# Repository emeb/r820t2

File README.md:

# r820t2
Breakout PCB design and STM32F0 firmware for the Rafael R820T2 tuner chip

Contents
--------

doc - documents for the chip and PCB design. This includes both the orginal
mfgs datasheet as well as schematic and BOM for the PCB design.

f030_r820t2 - STM32F030 firmware. A simple serial command line interface
to access registers and set frequency & gain parameters.

r820t2_breakout - KiCAD PCB design.

LICENSE
-------

The PCB design is licensed separately from the driver code. Please see
the LICENSE files within each sub-directory.

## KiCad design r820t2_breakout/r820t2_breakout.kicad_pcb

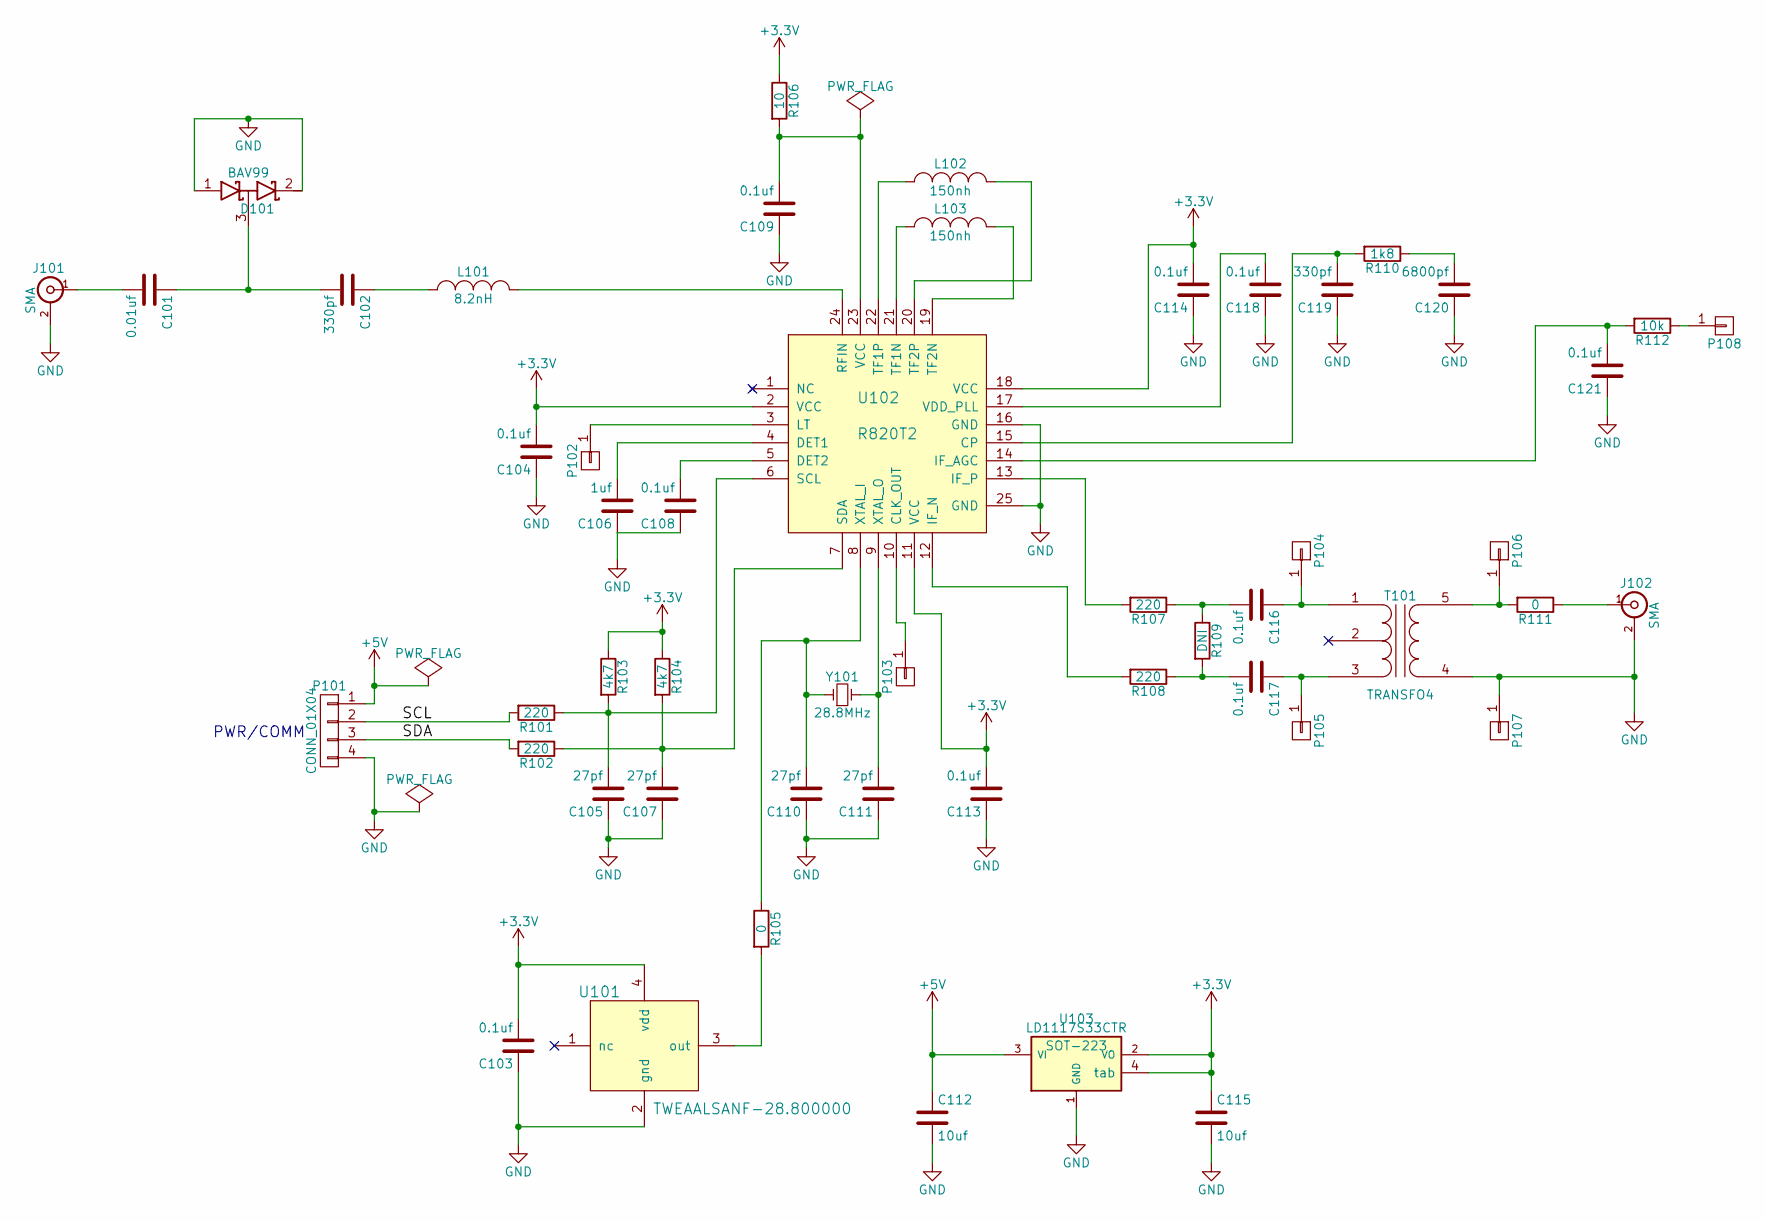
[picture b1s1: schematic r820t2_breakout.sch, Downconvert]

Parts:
C101: 0.01uf; C_0603_HandSoldering
C102, C119: 330pf; C_0603_HandSoldering
C103, C104, C108, C109, C113, C114, C116, C117, C118, C121: 0.1uf; C_0603_HandSoldering
C105, C107, C110, C111: 27pf; C_0603_HandSoldering
C106: 1uf; C_0603_HandSoldering
C112, C115: 10uf; C_0805_HandSoldering
C120: 6800pf; C_0603_HandSoldering
D101: BAV99; SOT-23
J101, J102: SMA; SMA_END
L101: 8.2nH; R_0603_HandSoldering
L102, L103: 150nh; R_0603_HandSoldering
P101: CONN_01X04; Pin_Header_Straight_1x04_Pitch2.54mm
P102, P103, P104, P105, P106, P107, P108: CONN_01X01; PINTST
R101, R102, R107, R108: 220; R_0603_HandSoldering
R103, R104: 4k7; R_0603_HandSoldering
R105, R111: 0; R_0603_HandSoldering
R106: 10; R_0603_HandSoldering
R109: DNI; R_0603_HandSoldering
R110: 1k8; R_0603_HandSoldering
R112: 10k; R_0603_HandSoldering
T101: TRANSFO4; Pulse_SMD_Balun
U101: TWEAALSANF-28.800000; Crystal_SMD_Abracon_ABM3C-4pin_5.0x3.2mm
U102: R820T2; QFN-24-1EP_4x4mm_Pitch0.5mm_extended_pad
U103: LD1117S33CTR; SOT-223
Y101: 28.8MHz; Crystal_SMD_HC49-SD

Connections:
+3V3: C103.2, C104.2, C113.2, C114.2, C115.1, R103.1, R104.1, R106.1, U101.4 (vdd), U102.2 (VCC), U102.11 (VCC), U102.18 (VCC), U103.2 (VO), U103.4 (tab)
+5V: C112.1, P101.1, U103.3 (VI)
/SCL: P101.2, R101.2
/SDA: P101.3, R102.2
GND: C103.1, C104.1, C105.1, C106.1, C107.1, C108.1, C109.1, C110.1, C111.1, C112.2, C113.1, C114.1, C115.2, C118.1, C119.1, C120.1, C121.1, D101.1 (A), D101.2 (K), J101.2 (Ext), J102.2 (Ext), P101.4, P107.1, T101.4 (S1), U101.2 (gnd), U102.16 (GND), U102.25 (GND), U103.1 (GND)
unnamed: C101.1, C102.2, D101.3 (common)
unnamed: C101.2, J101.1 (In)
unnamed: C102.1, L101.1
unnamed: C105.2, R101.1, R103.2, U102.6 (SCL)
unnamed: C106.2, U102.4 (DET1)
unnamed: C107.2, R102.1, R104.2, U102.7 (SDA)
unnamed: C108.2, U102.5 (DET2)
unnamed: C109.2, R106.2, U102.23 (VCC)
unnamed: C110.2, R105.1, U102.8 (XTAL_I), Y101.1
unnamed: C111.2, U102.9 (XTAL_O), Y101.2
unnamed: C116.1, P104.1, T101.1 (PR1)
unnamed: C116.2, R107.1, R109.1
unnamed: C117.1, P105.1, T101.3 (PR2)
unnamed: C117.2, R108.1, R109.2
unnamed: C118.2, U102.17 (VDD_PLL)
unnamed: C119.2, R110.2, U102.15 (CP)
unnamed: C120.2, R110.1
unnamed: C121.2, R112.2, U102.14 (IF_AGC)
unnamed: J102.1 (In), R111.1
unnamed: L101.2, U102.24 (RFIN)
unnamed: L102.1, U102.20 (TF2P)
unnamed: L102.2, U102.22 (TF1P)
unnamed: L103.1, U102.19 (TF2N)
unnamed: L103.2, U102.21 (TF1N)
unnamed: P102.1, U102.3 (LT)
unnamed: P103.1, U102.10 (CLK_OUT)
unnamed: P106.1, R111.2, T101.5 (S2)
unnamed: P108.1, R112.1
unnamed: R105.2, U101.3 (out)
unnamed: R107.2, U102.13 (IF_P)
unnamed: R108.2, U102.12 (IF_N)

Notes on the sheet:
PWR/COMM

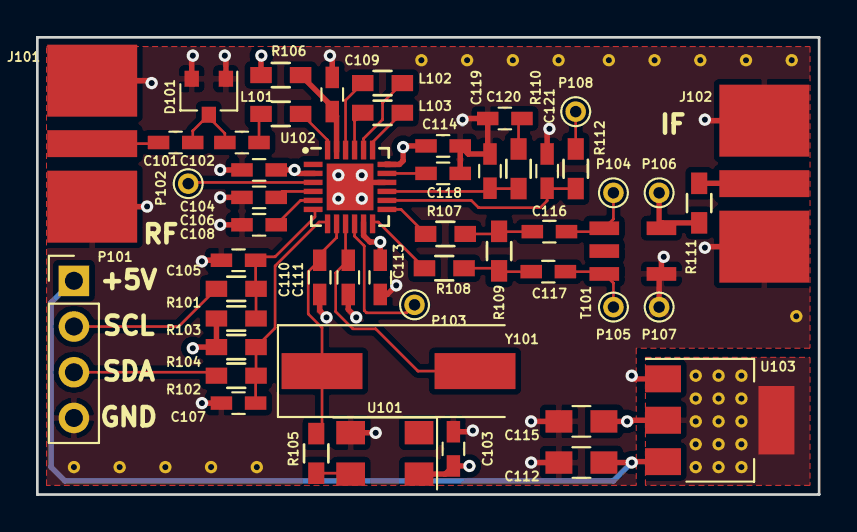
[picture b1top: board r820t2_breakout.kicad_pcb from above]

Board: 4 copper layers, 43.4 x 25.4 mm, 52 parts (0 on the bottom side), 36 nets.

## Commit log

2017-02-17 Initial code commit
2017-02-17 Clarify licensing
2017-02-17 Moved top level MIT license to KiCAD project
2017-02-17 Notes on licensing
2018-09-30 Fix out of bounds read in R820T2_init procedure

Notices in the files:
r820t2_breakout/r820t2_breakout.kicad_pcb:
(c) 2017 E. Brombaugh
